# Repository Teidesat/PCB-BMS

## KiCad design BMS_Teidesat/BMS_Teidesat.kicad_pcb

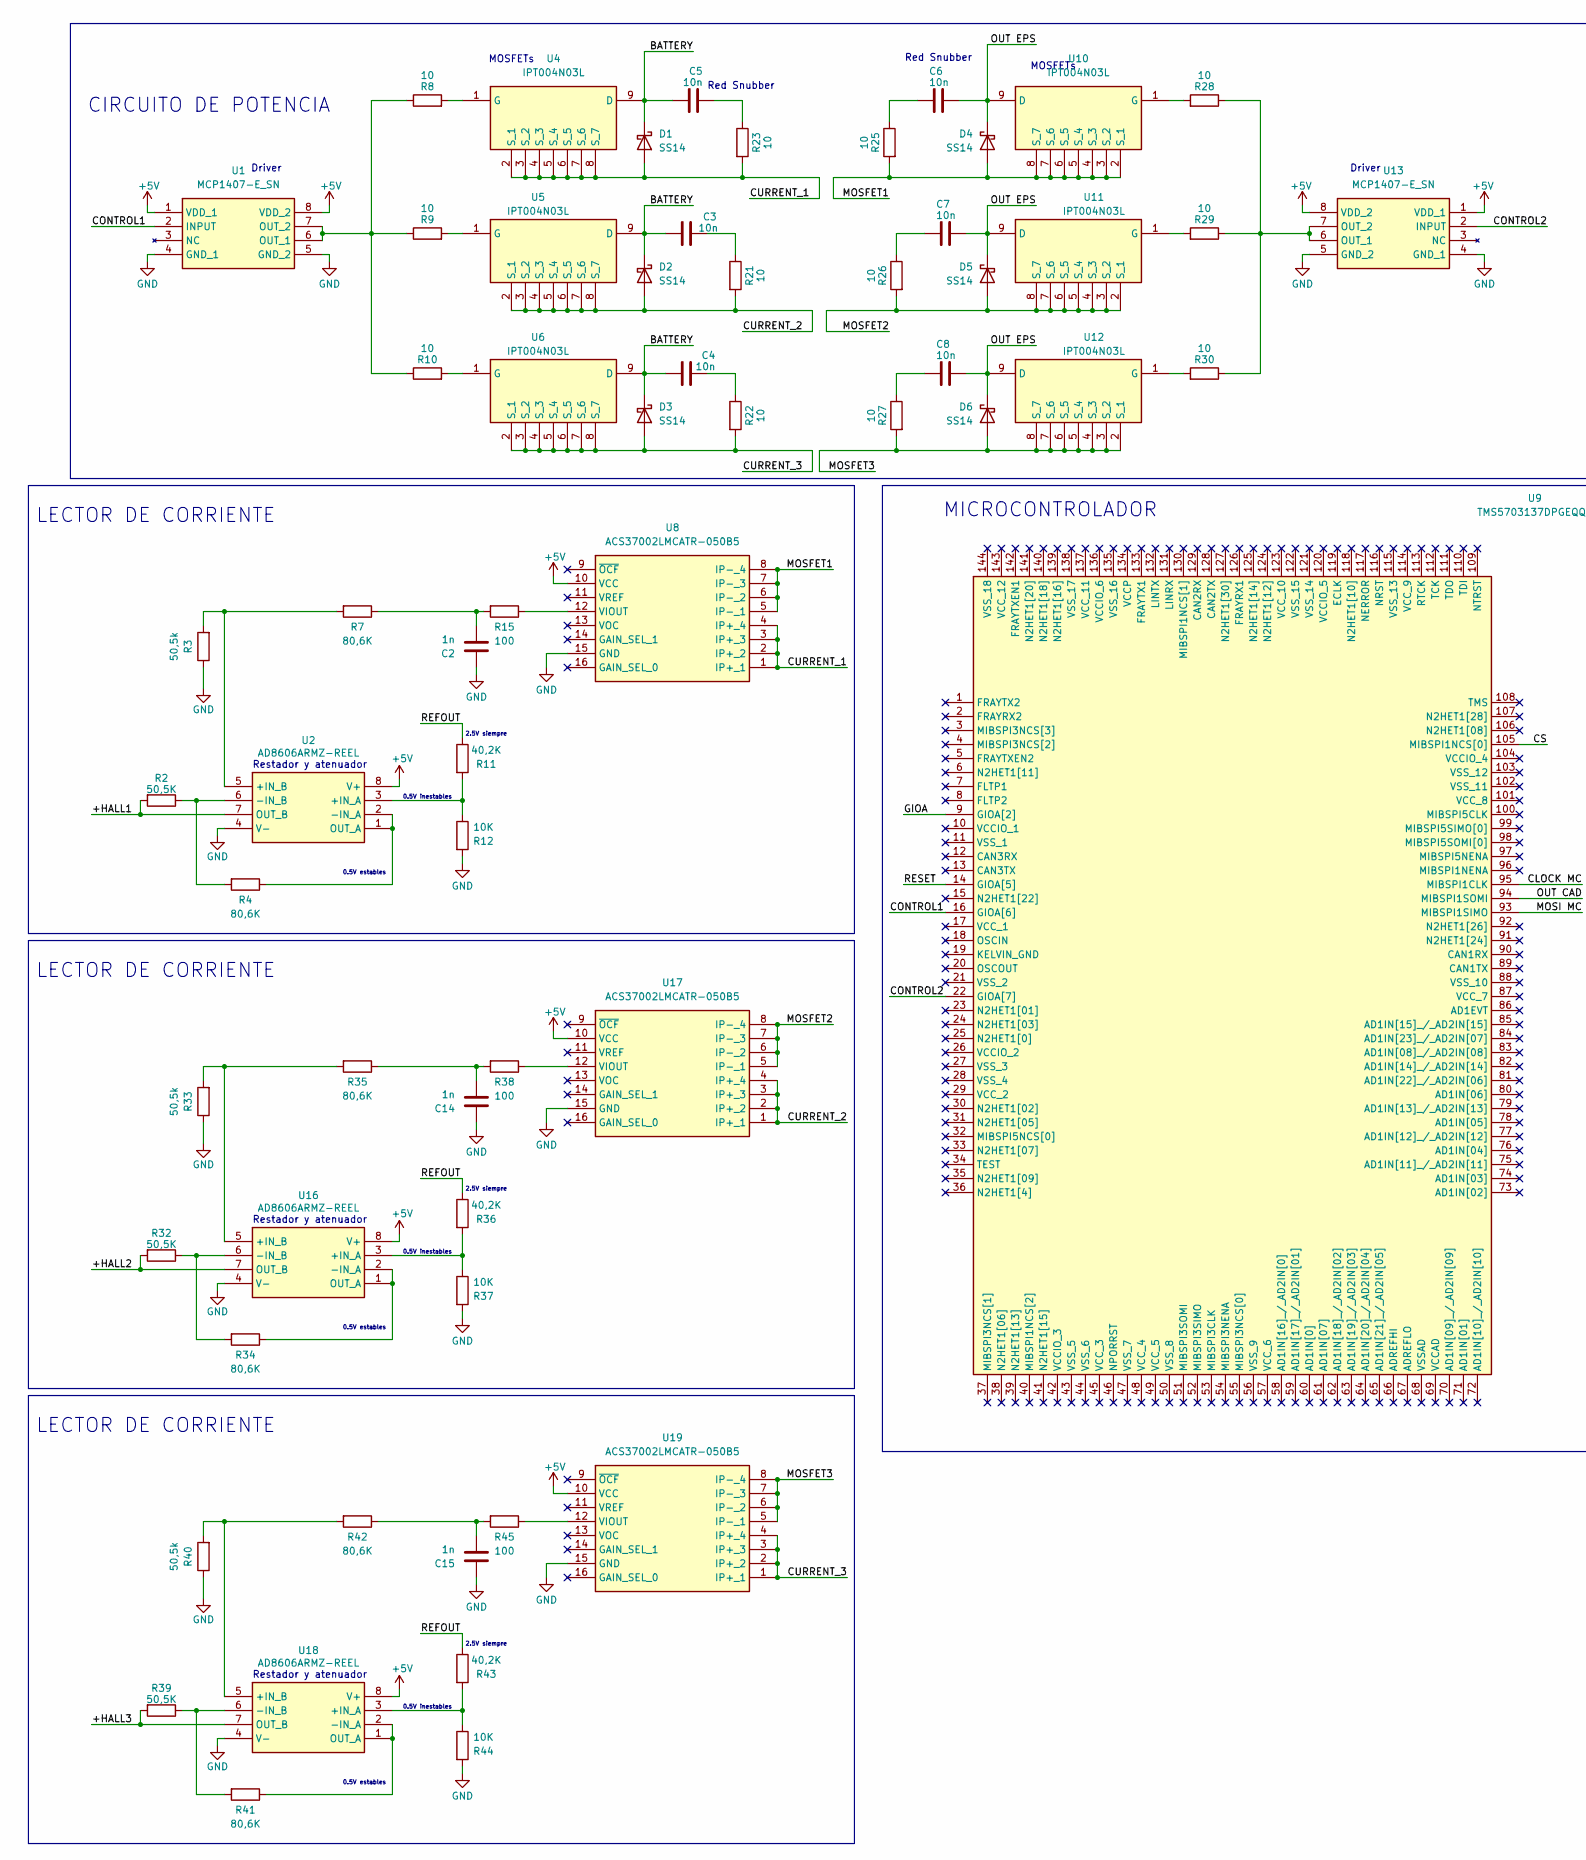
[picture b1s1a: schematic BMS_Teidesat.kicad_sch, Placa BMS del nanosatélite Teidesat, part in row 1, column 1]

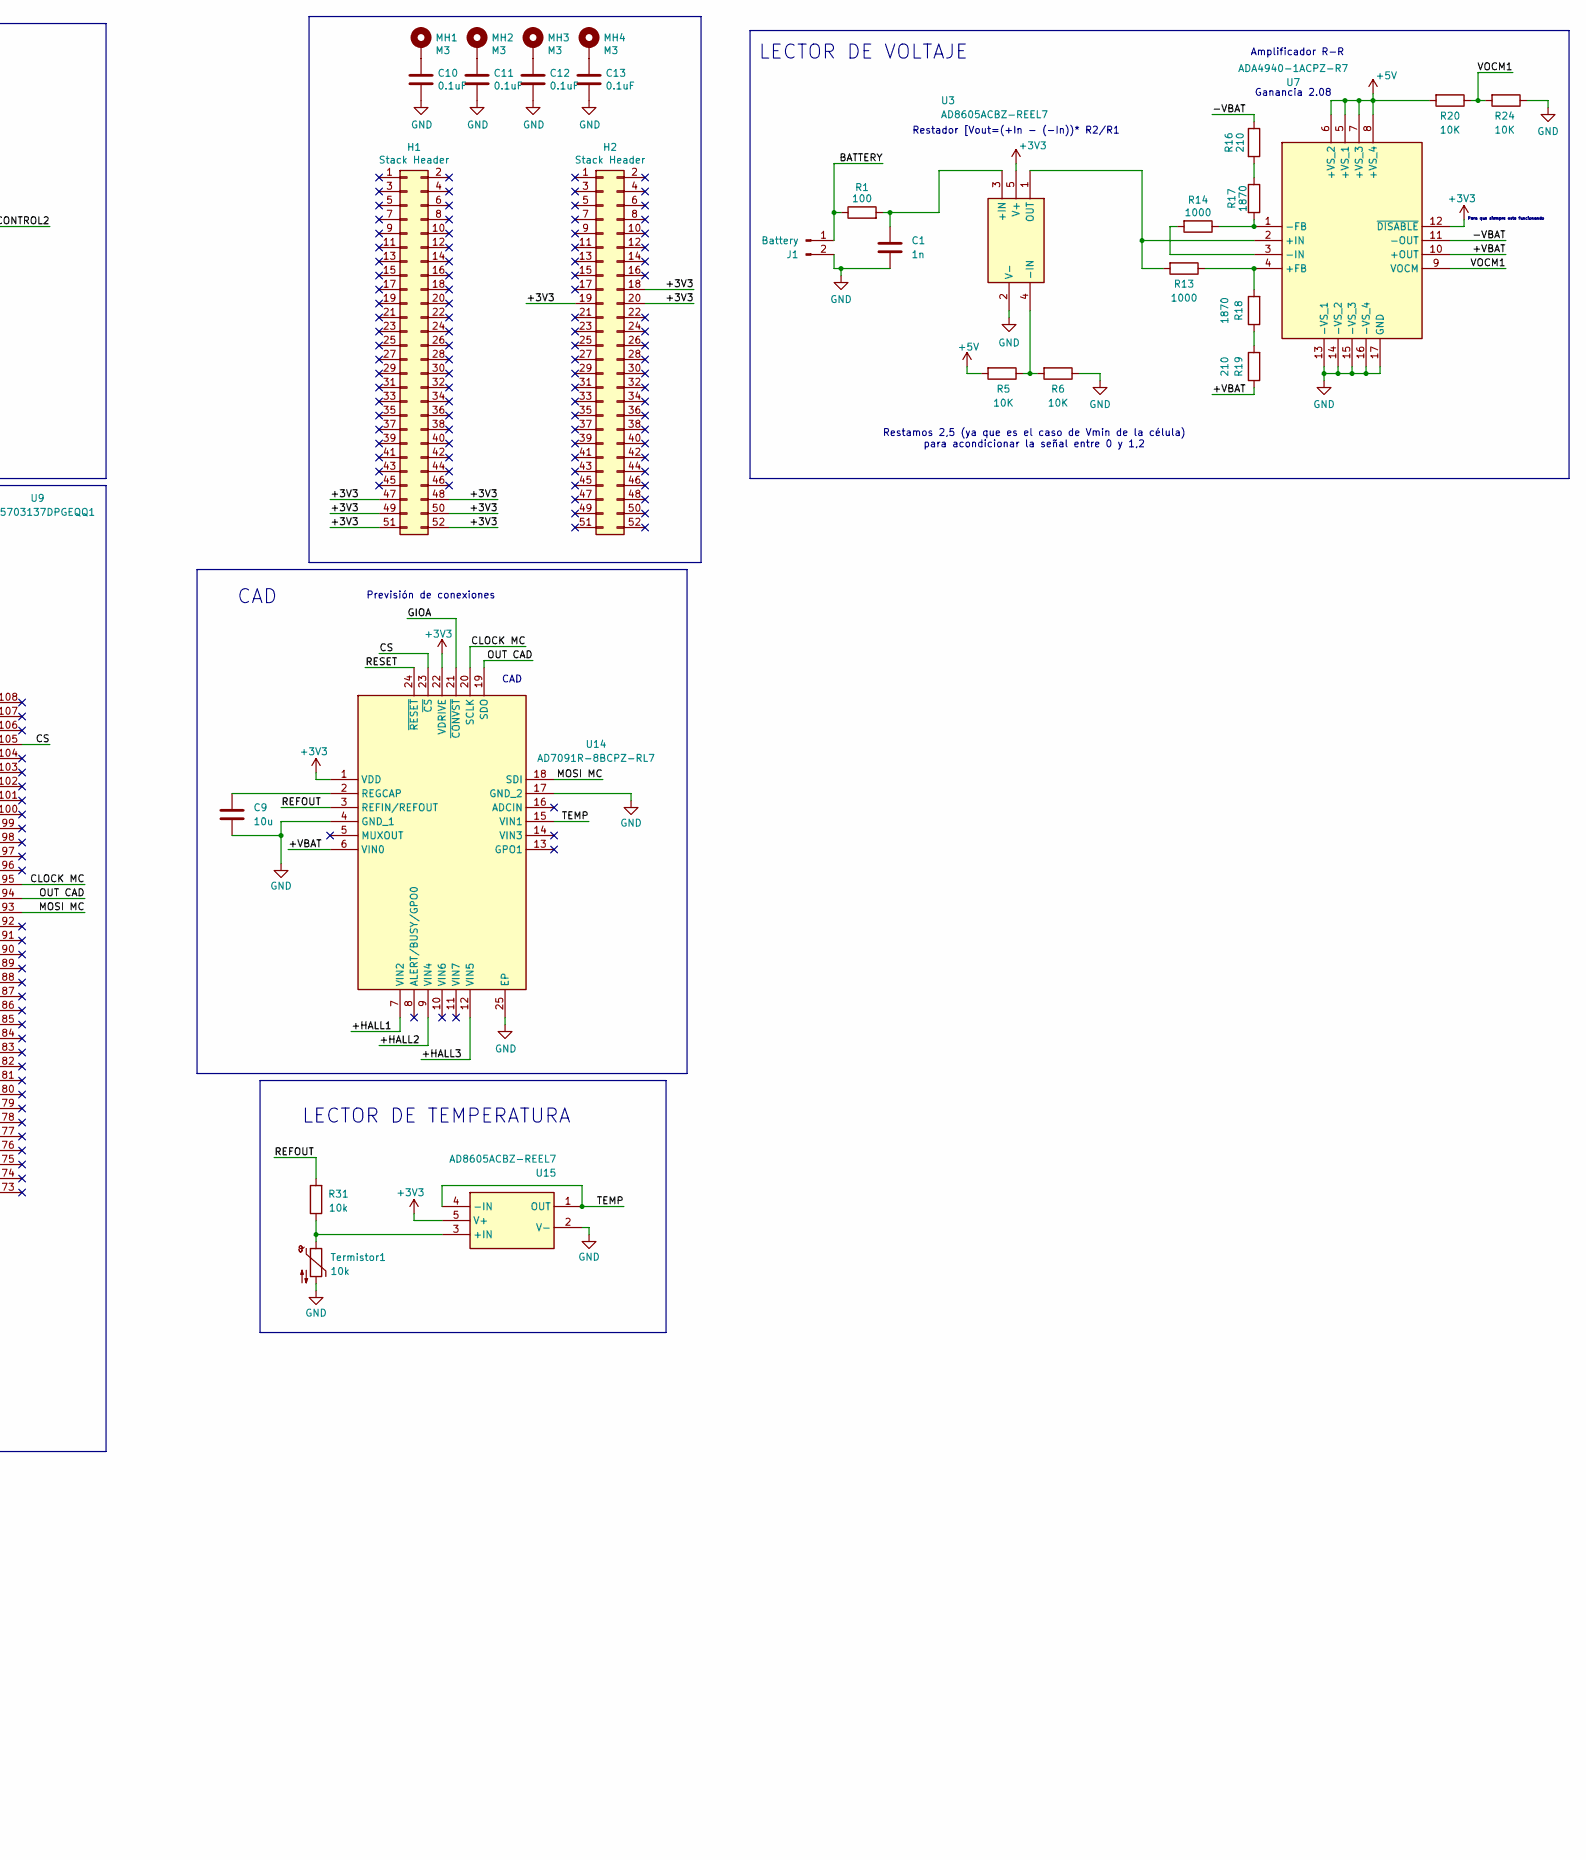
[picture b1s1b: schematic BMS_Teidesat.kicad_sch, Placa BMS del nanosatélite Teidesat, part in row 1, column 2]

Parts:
C1, C2, C14, C15: 1n; C_0805_2012Metric
C3, C4, C5, C6, C7, C8: 10n; C_0805_2012Metric
C9: 10u; C_0805_2012Metric
C10, C11, C12, C13: 0.1uF; C_0805_2012Metric
D1, D2, D3, D4, D5, D6: SS14; DIOM8059X256N
H1, H2: Stack Header; PinHeader_2x26_P2.54mm_Vertical
J1: Battery; PinSocket_1x02_P1.00mm_Vertical_SMD_Pin1Left
MH1, MH2, MH3, MH4: M3; MountingHole_3.2mm_M3_Pad
R1, R15, R38, R45: 100; R_0201_0603Metric
R2, R32, R39: 50,5K; R_0201_0603Metric
R3, R33, R40: 50,5k; R_0201_0603Metric
R4, R7, R34, R35, R41, R42: 80,6K; R_0201_0603Metric
R5, R6, R12, R20, R24, R37, R44: 10K; R_0201_0603Metric
R8, R9, R10, R21, R22, R23, R25, R26, R27, R28, R29, R30: 10; R_0201_0603Metric
R11, R36, R43: 40,2K; R_0201_0603Metric
R13, R14: 1000; R_0201_0603Metric
R16, R19: 210; R_0201_0603Metric
R17, R18: 1870; R_0201_0603Metric
R31: 10k; R_0201_0603Metric
Termistor1: 10k; R_0201_0603Metric
U1, U13: MCP1407-E_SN; SOIC127P600X175-8N; Mouser Part Number 579-MCP1407-E/SN
U2, U16, U18: AD8606ARMZ-REEL; SOP65P490X110-8N; Mouser Part Number 584-AD8606ARMZ-R
U3, U15: AD8605ACBZ-REEL7; AD8605ACBZREEL7; Mouser Part Number 584-AD8605ACBZ-R7
U4, U5, U6, U10, U11, U12: IPT004N03L; PG-HSOF-8-1; Mouser Part Number 726-IPT004N03L
U7: ADA4940-1ACPZ-R7; QFN50P300X300X80-17N-D; Mouser Part Number 584-ADA4940-1ACPZ-R7
U8, U17, U19: ACS37002LMCATR-050B5; ACS37002LMCA050U5; Mouser Part Number 250-2LMCATR-050B5
U9: TMS5703137DPGEQQ1; QFP50P2200X2200X160-144N; Manufacturer_Part_Number TMS5703137DPGEQQ1; Mouser Part Number 595-MS5703137DPGEQQ1
U14: AD7091R-8BCPZ-RL7; QFN50P400X400X80-25N-D; Mouser Part Number 584-AD7091R-8BCPZRL7

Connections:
+3V3: H1.47, H1.48, H1.49, H1.50, H1.51, H1.52, H2.18, H2.19, H2.20, U3.5 (V+), U7.12 (~DISABLE), U14.1 (VDD), U14.22 (VDRIVE), U15.5 (V+)
+5V: R5.2, R20.2, U1.1 (VDD_1), U1.8 (VDD_2), U2.8 (V+), U7.5 (+VS_1), U7.6 (+VS_2), U7.7 (+VS_3), U7.8 (+VS_4), U8.10 (VCC), U13.1 (VDD_1), U13.8 (VDD_2), U16.8 (V+), U17.10 (VCC), U18.8 (V+), U19.10 (VCC)
/+HALL1: R2.2, U2.7 (OUT_B), U14.7 (VIN2)
/+HALL2: R32.2, U14.9 (VIN4), U16.7 (OUT_B)
/+HALL3: R39.2, U14.12 (VIN5), U18.7 (OUT_B)
/+VBAT: R19.1, U7.10 (+OUT), U14.6 (VIN0)
/-VBAT: R16.1, U7.11 (-OUT)
/BATTERY: C3.1, C4.1, C5.1, D1.1 (K), D2.1 (K), D3.1 (K), J1.1, R1.1, U4.9 (D), U5.9 (D), U6.9 (D)
/CLOCK MC: U9.95 (MIBSPI1CLK), U14.20 (SCLK)
/CONTROL1: U1.2 (INPUT), U9.16 (GIOA[6])
/CONTROL2: U9.22 (GIOA[7]), U13.2 (INPUT)
/CS: U9.105 (MIBSPI1NCS[0]), U14.23 (~CS)
/CURRENT_1: D1.2 (A), R23.2, U4.2 (S_1), U4.3 (S_2), U4.4 (S_3), U4.5 (S_4), U4.6 (S_5), U4.7 (S_6), U4.8 (S_7), U8.1 (IP+_1), U8.2 (IP+_2), U8.3 (IP+_3), U8.4 (IP+_4)
/CURRENT_2: D2.2 (A), R21.2, U5.2 (S_1), U5.3 (S_2), U5.4 (S_3), U5.5 (S_4), U5.6 (S_5), U5.7 (S_6), U5.8 (S_7), U17.1 (IP+_1), U17.2 (IP+_2), U17.3 (IP+_3), U17.4 (IP+_4)
/CURRENT_3: D3.2 (A), R22.2, U6.2 (S_1), U6.3 (S_2), U6.4 (S_3), U6.5 (S_4), U6.6 (S_5), U6.7 (S_6), U6.8 (S_7), U19.1 (IP+_1), U19.2 (IP+_2), U19.3 (IP+_3), U19.4 (IP+_4)
/GIOA: U9.9 (GIOA[2]), U14.21 (~CONVST)
/MOSFET1: D4.2 (A), R25.2, U8.5 (IP-_1), U8.6 (IP-_2), U8.7 (IP-_3), U8.8 (IP-_4), U10.2 (S_1), U10.3 (S_2), U10.4 (S_3), U10.5 (S_4), U10.6 (S_5), U10.7 (S_6), U10.8 (S_7)
/MOSFET2: D5.2 (A), R26.2, U11.2 (S_1), U11.3 (S_2), U11.4 (S_3), U11.5 (S_4), U11.6 (S_5), U11.7 (S_6), U11.8 (S_7), U17.5 (IP-_1), U17.6 (IP-_2), U17.7 (IP-_3), U17.8 (IP-_4)
/MOSFET3: D6.2 (A), R27.2, U12.2 (S_1), U12.3 (S_2), U12.4 (S_3), U12.5 (S_4), U12.6 (S_5), U12.7 (S_6), U12.8 (S_7), U19.5 (IP-_1), U19.6 (IP-_2), U19.7 (IP-_3), U19.8 (IP-_4)
/MOSI MC: U9.93 (MIBSPI1SIMO), U14.18 (SDI)
/OUT CAD: U9.94 (MIBSPI1SOMI), U14.19 (SDO)
/OUT EPS: C6.1, C7.1, C8.1, D4.1 (K), D5.1 (K), D6.1 (K), U10.9 (D), U11.9 (D), U12.9 (D)
/REFOUT: R11.1, R31.2, R36.1, R43.1, U14.3 (REFIN/REFOUT)
/RESET: U9.14 (GIOA[5]), U14.24 (~RESET)
/TEMP: U14.15 (VIN1), U15.1 (OUT), U15.4 (-IN)
/VOCM1: R20.1, R24.2, U7.9 (VOCM)
GND: C1.2, C2.1, C9.2, C10.2, C11.2, C12.2, C13.2, C14.1, C15.1, J1.2, R3.1, R6.1, R12.2, R24.1, R33.1, R37.2, R40.1, R44.2, Termistor1.2, U1.4 (GND_1), U1.5 (GND_2), U2.4 (V-), U3.2 (V-), U7.13 (-VS_1), U7.14 (-VS_2), U7.15 (-VS_3), U7.16 (-VS_4), U7.17 (GND), U8.15 (GND), U13.4 (GND_1), U13.5 (GND_2), U14.4 (GND_1), U14.17 (GND_2), U14.25 (EP), U15.2 (V-), U16.4 (V-), U17.15 (GND), U18.4 (V-), U19.15 (GND)
unnamed: C2.2, R7.1, R15.2
unnamed: C3.2, R21.1
unnamed: C4.2, R22.1
unnamed: C5.2, R23.1
unnamed: C6.2, R25.1
unnamed: C7.2, R26.1
unnamed: C8.2, R27.1
unnamed: C10.1, MH1.1
unnamed: C11.1, MH2.1
unnamed: C12.1, MH3.1
unnamed: C13.1, MH4.1
unnamed: C14.2, R35.1, R38.2
unnamed: C15.2, R42.1, R45.2
unnamed: R16.2, R17.1
unnamed: R18.1, R19.2
unnamed: R8.1, R9.1, R10.1, U1.6 (OUT_1), U1.7 (OUT_2)
unnamed: R11.2, R12.1, U2.3 (+IN_A)
unnamed: R3.2, R7.2, U2.5 (+IN_B)
unnamed: R4.1, U2.1 (OUT_A), U2.2 (-IN_A)
unnamed: R2.1, R4.2, U2.6 (-IN_B)
unnamed: C1.1, R1.2, U3.3 (+IN)
unnamed: R5.1, R6.2, U3.4 (-IN)
unnamed: R13.2, U3.1 (OUT), U7.2 (+IN)
unnamed: R8.2, U4.1 (G)
unnamed: R9.2, U5.1 (G)
unnamed: R10.2, U6.1 (G)
unnamed: R13.1, R18.2, U7.4 (+FB)
unnamed: R14.1, R17.2, U7.1 (-FB)
unnamed: R14.2, U7.3 (-IN)
unnamed: R15.1, U8.12 (VIOUT)
unnamed: R28.2, U10.1 (G)
unnamed: R29.2, U11.1 (G)
unnamed: R30.2, U12.1 (G)
unnamed: R28.1, R29.1, R30.1, U13.6 (OUT_1), U13.7 (OUT_2)
unnamed: C9.1, U14.2 (REGCAP)
unnamed: R31.1, Termistor1.1, U15.3 (+IN)
unnamed: R36.2, R37.1, U16.3 (+IN_A)
unnamed: R33.2, R35.2, U16.5 (+IN_B)
unnamed: R34.1, U16.1 (OUT_A), U16.2 (-IN_A)
unnamed: R32.1, R34.2, U16.6 (-IN_B)
unnamed: R38.1, U17.12 (VIOUT)
unnamed: R43.2, R44.1, U18.3 (+IN_A)
unnamed: R40.2, R42.2, U18.5 (+IN_B)
unnamed: R41.1, U18.1 (OUT_A), U18.2 (-IN_A)
unnamed: R39.1, R41.2, U18.6 (-IN_B)
unnamed: R45.1, U19.12 (VIOUT)

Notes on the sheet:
Amplificador R-R
MICROCONTROLADOR
2.5V siempre
LECTOR DE CORRIENTE
LECTOR DE TEMPERATURA
Restador y atenuador
Driver
Para que siempre este funcionando
CAD
Previsión de conexiones
0.5V inestables
0.5V estables
CIRCUITO DE POTENCIA
Ganancia 2.08
MOSFETs
LECTOR DE VOLTAJE
Restamos 2,5 (ya que es el caso de Vmin de la célula) para acondicionar la señal entre 0 y 1,2
Red Snubber
Restador [Vout=(+In - (-In))* R2/R1
CAD

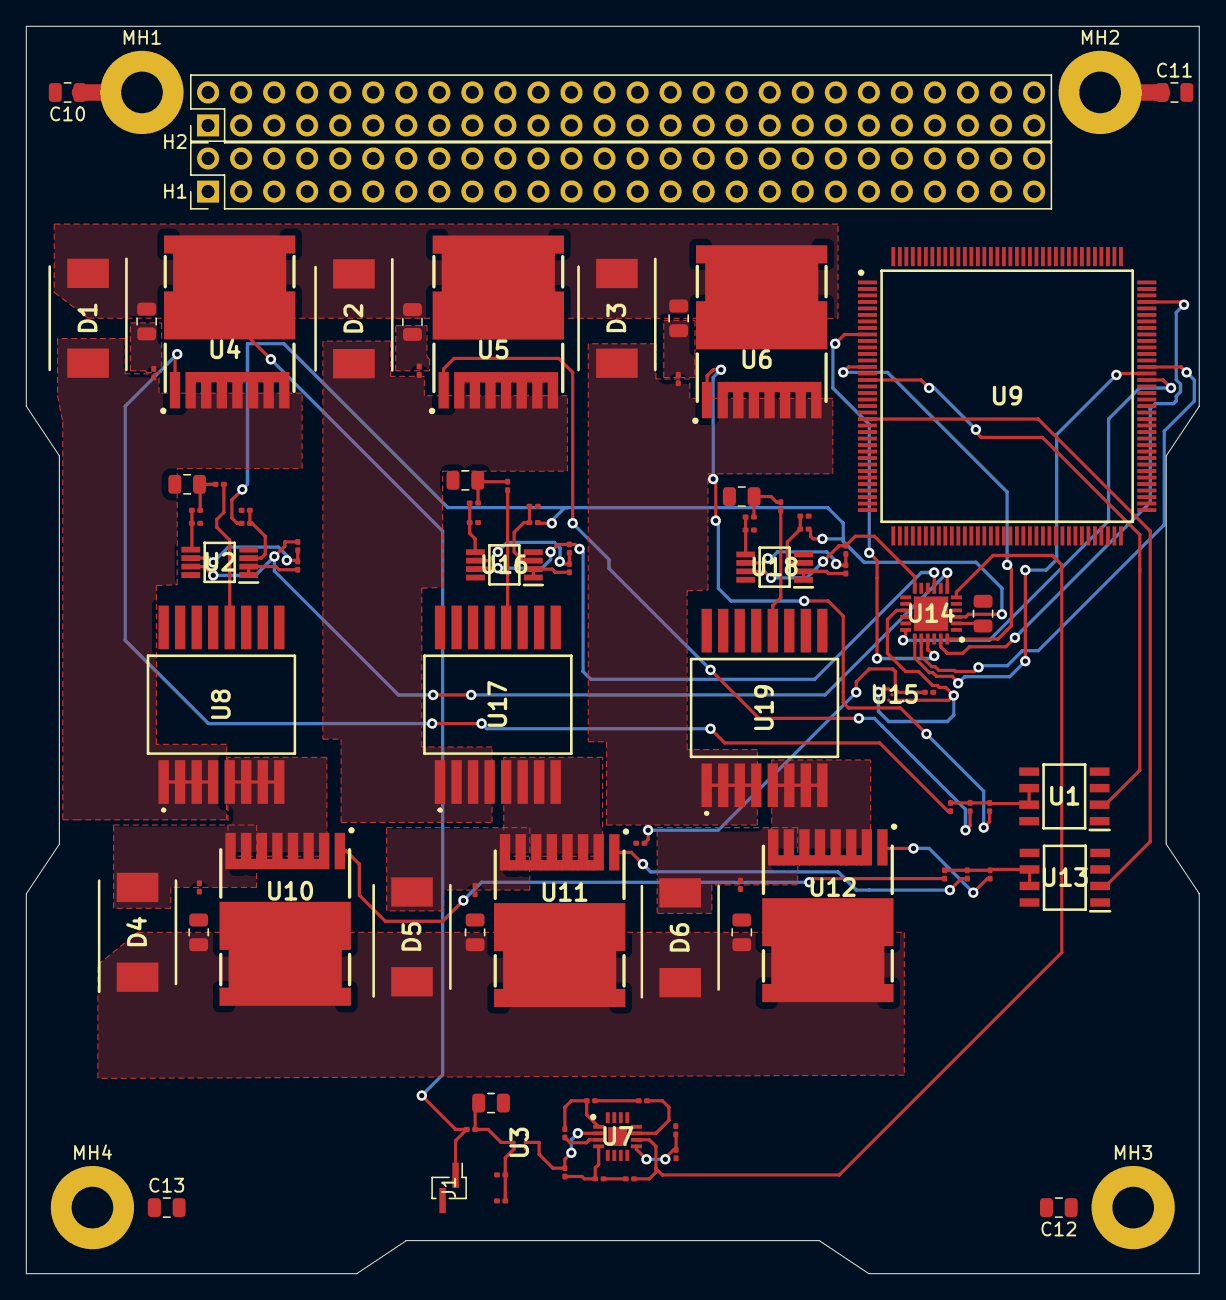
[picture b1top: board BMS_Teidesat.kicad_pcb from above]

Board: 2 copper layers, 90.2 x 95.9 mm, 93 parts (0 on the bottom side), 73 nets.

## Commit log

2025-10-30 Create BMS_Teidesat.kicad_sch
    Primer esquemático del BMS
2025-10-31 Create BMS_Teidesat.kicad_sch
    Primer esquemático con restador y comienzo con la sonda Hall
2025-10-31 Carpeta Completa
    Toda la carpeta del primer esquemático
2025-11-01 Add .gitignore to exclude temporary and export files
2025-11-01 Esquemático 2
    Se finalizó la rama del amplificador R-R añadiendo al ganancia final y se comenzó con la rama de la sonda Hall
2025-11-02 Actualización de esquemático
    Se ha terminado el circuito de lectura de temperatura, el circuito de potencia y el conexionado del CAD (en principio)
2025-11-03 Esquemático 3
    Implementados los arreglos propuestos por Salvador y añadido el microcontrolador
2025-11-05 Eliminar archivos innecesarios
2025-11-05 Eliminar archivos
2025-11-06 Modificación de etiquetas y nuevo micro
    Se han puesto correctamente las etiquetas, todas en ingles en mayúsculas y con el cable debajo. Además de poner el correcto símbolo y huella del micro
2025-11-12 Conexiones micro y sensor de corriente implementado
    Conectamos el sensor de corriente entre los MOSFETS del circuito de potencia y conectamos el CAD al microcontrolador
2025-11-12 Conexión MOSFET al micro
2025-11-12 Quitar el .gitignore
2025-11-13 Comienzo de enrutado
2025-11-14 Se ha hecho un primer conexionado de la PCB
2025-11-17 Arreglos de trackeo
2025-11-18 Actualización gitignore
2025-11-18 Limpieza de archivos
2025-11-22 Se ha corregido el enrutado de la PCB. Faltan las conexiones de alimentación y de tierra
2025-11-29 Nuevo circuito de potencia
    Hemos tenido que rediseñar el circuito de potencia, añadiendo nuevos MOSFETS y drivers para dividir la corriente entre 3 y evitar problemas de sobrecalentamiento
2025-12-03 Salida EPS añadida
2025-12-08 Ajustes PCB
2025-12-08 Circuito de potencia PCB
    Se ha elaborado el circuito de potencia de en la PCB incorporando los 3 mosfets y los 3 sensores de temperatura.
